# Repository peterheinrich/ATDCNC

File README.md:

# ATDCNC
A Tiny Desktop CNC Built from Readily Available Parts

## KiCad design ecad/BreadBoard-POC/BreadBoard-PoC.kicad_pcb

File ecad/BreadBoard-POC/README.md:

# GRBL Compatible Controller

This tiny desktop CNC will use GRBL to interpret G-Code.

## PoC Breadboard Setup
* Uses now obsolete L6208N (PDIP) stepper driver. L6208D is still available for SMD design iteration. Basically any step/dir driver will do!
* 1.5A max phase current with a 20V supply for sufficient headroom.
* ATMega328 microcontroller for step generation.
* 2.54mm (100mil) design restriction for easy breadboard prototyping.

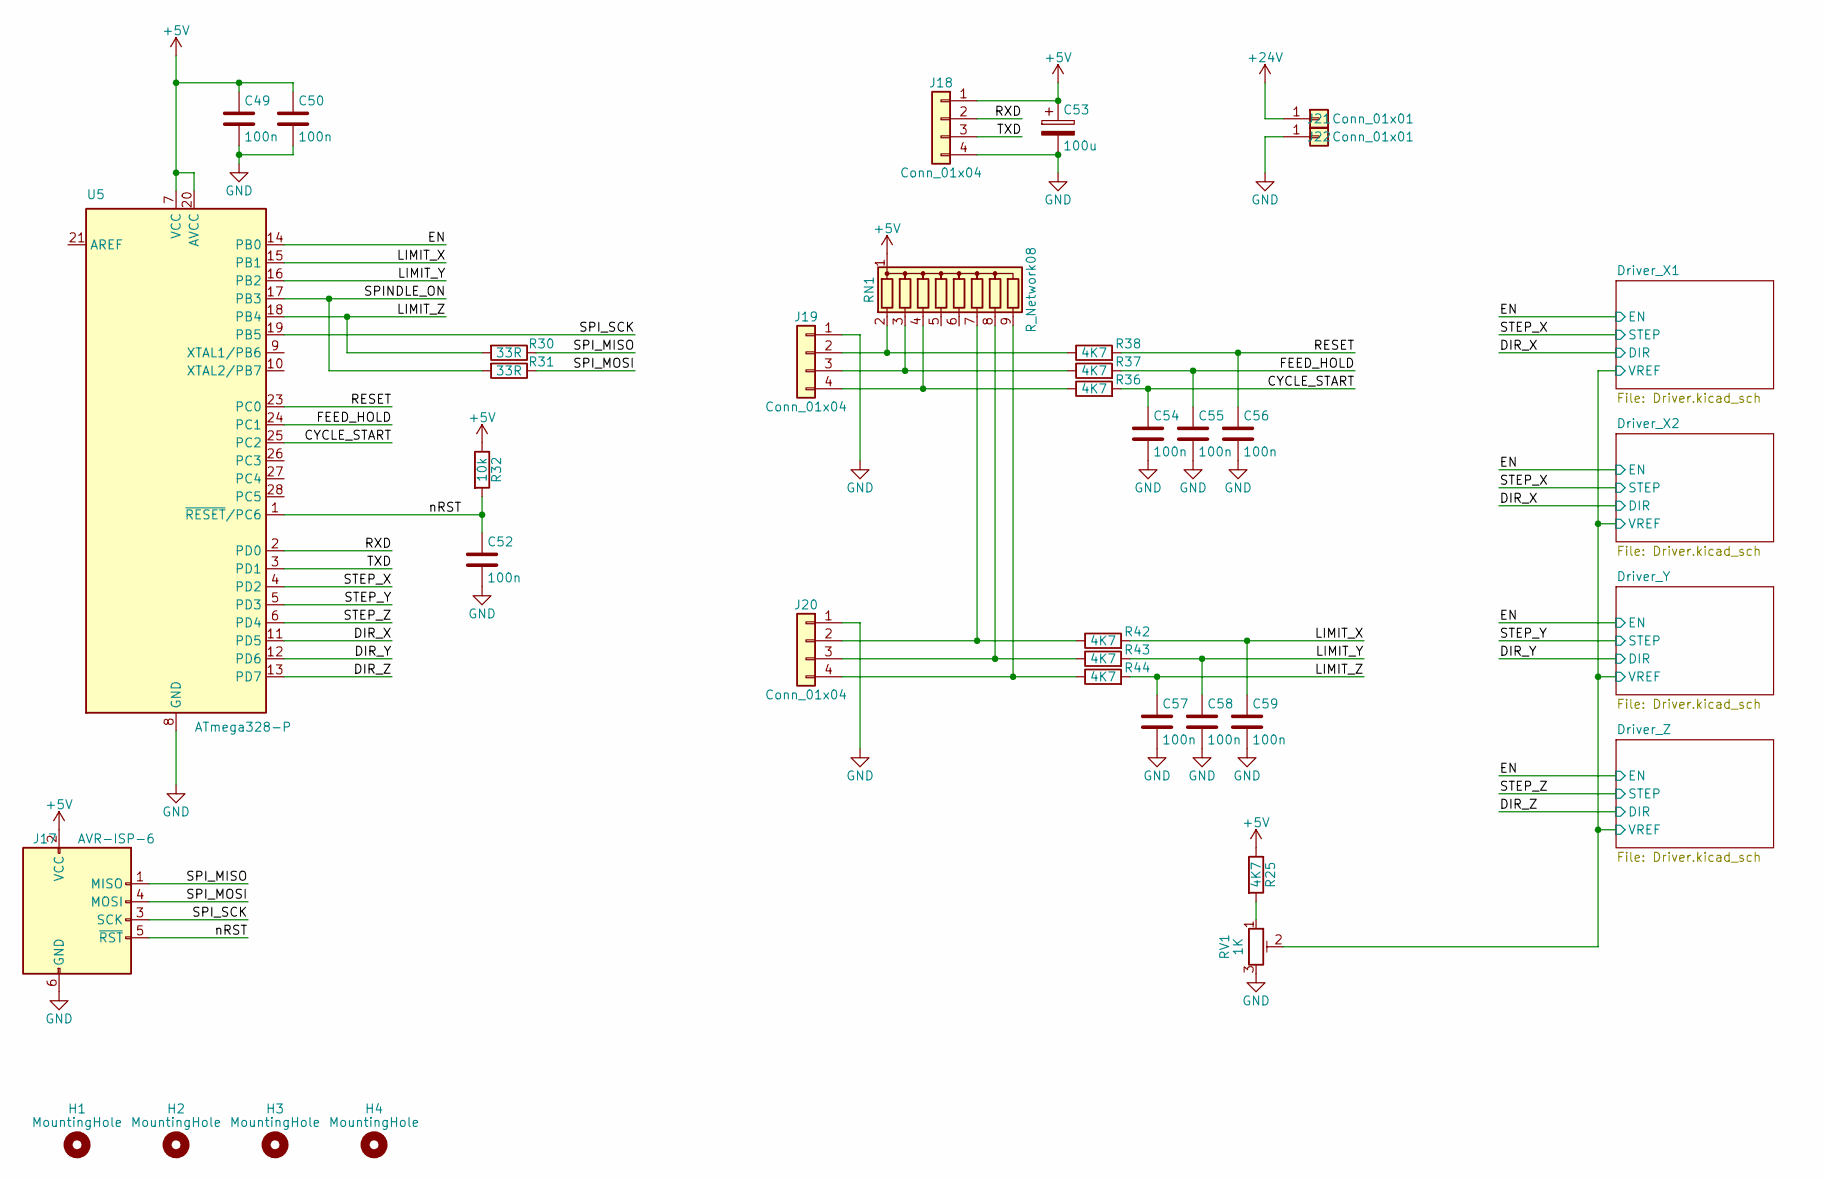
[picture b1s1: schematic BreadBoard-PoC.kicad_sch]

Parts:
C49, C50, C52, C54, C55, C56, C57, C58, C59: 100n; C_Rect_L4.6mm_W2.0mm_P2.50mm_MKS02_FKP02
C53: 100u; CP_Radial_D6.3mm_P2.50mm
H1, H2, H3, H4: MountingHole; MountingHole_3.2mm_M3_DIN965
J17: AVR-ISP-6; PinHeader_2x03_P2.54mm_Vertical
J18, J19, J20: Conn_01x04; PinHeader_1x04_P2.54mm_Vertical
J21, J22: Conn_01x01; PinHeader_1x01_P2.54mm_Vertical
R25, R36, R37, R38, R42, R43, R44: 4K7; R_Axial_DIN0207_L6.3mm_D2.5mm_P2.54mm_Vertical
R30, R31: 33R; R_Axial_DIN0207_L6.3mm_D2.5mm_P2.54mm_Vertical
R32: 10k; R_Axial_DIN0207_L6.3mm_D2.5mm_P2.54mm_Vertical
RN1: R_Network08; R_Array_SIP9
RV1: 1K; Potentiometer_Bourns_3266W_Vertical
U5: ATmega328-P; DIP-28_W7.62mm_LongPads

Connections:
+5V: C49.1, C50.1, C53.1, J17.2 (VCC), J18.1, R25.1, R32.1, RN1.1 (common), U5.7 (VCC), U5.20 (AVCC); also elsewhere on the board
+24V: J21.1; also elsewhere on the board
/CYCLE_START: C54.1, R36.2, U5.25 (PC2)
/DIR_X: U5.11 (PD5); also elsewhere on the board
/DIR_Y: U5.12 (PD6); also elsewhere on the board
/DIR_Z: U5.13 (PD7); also elsewhere on the board
/Driver_X1/VREF: RV1.2; also elsewhere on the board
/EN: U5.14 (PB0); also elsewhere on the board
/FEED_HOLD: C55.1, R37.2, U5.24 (PC1)
/LIMIT_X: C59.1, R42.2, U5.15 (PB1)
/LIMIT_Y: C58.1, R43.2, U5.16 (PB2)
/LIMIT_Z: C57.1, R30.2, R44.2, U5.18 (PB4)
/RESET: C56.1, R38.2, U5.23 (PC0)
/RXD: J18.2, U5.2 (PD0)
/SPINDLE_ON: R31.2, U5.17 (PB3)
/SPI_MISO: J17.1 (MISO), R30.1
/SPI_MOSI: J17.4 (MOSI), R31.1
/SPI_SCK: J17.3 (SCK), U5.19 (PB5)
/STEP_X: U5.4 (PD2); also elsewhere on the board
/STEP_Y: U5.5 (PD3); also elsewhere on the board
/STEP_Z: U5.6 (PD4); also elsewhere on the board
/TXD: J18.3, U5.3 (PD1)
/nRST: C52.1, J17.5 (~RST), R32.2, U5.1 (~RESET/PC6)
GND: C49.2, C50.2, C52.2, C53.2, C54.2, C55.2, C56.2, C57.2, C58.2, C59.2, J17.6 (GND), J18.4, J19.1, J20.1, J22.1, RV1.3, U5.8 (GND), U5.22 (GND); also elsewhere on the board
unnamed: J19.2, R38.1, RN1.2 (R1)
unnamed: J19.3, R37.1, RN1.3 (R2)
unnamed: J19.4, R36.1, RN1.4 (R3)
unnamed: J20.2, R42.1, RN1.7 (R6)
unnamed: J20.3, R43.1, RN1.8 (R7)
unnamed: J20.4, R44.1, RN1.9 (R8)
unnamed: R25.2, RV1.1

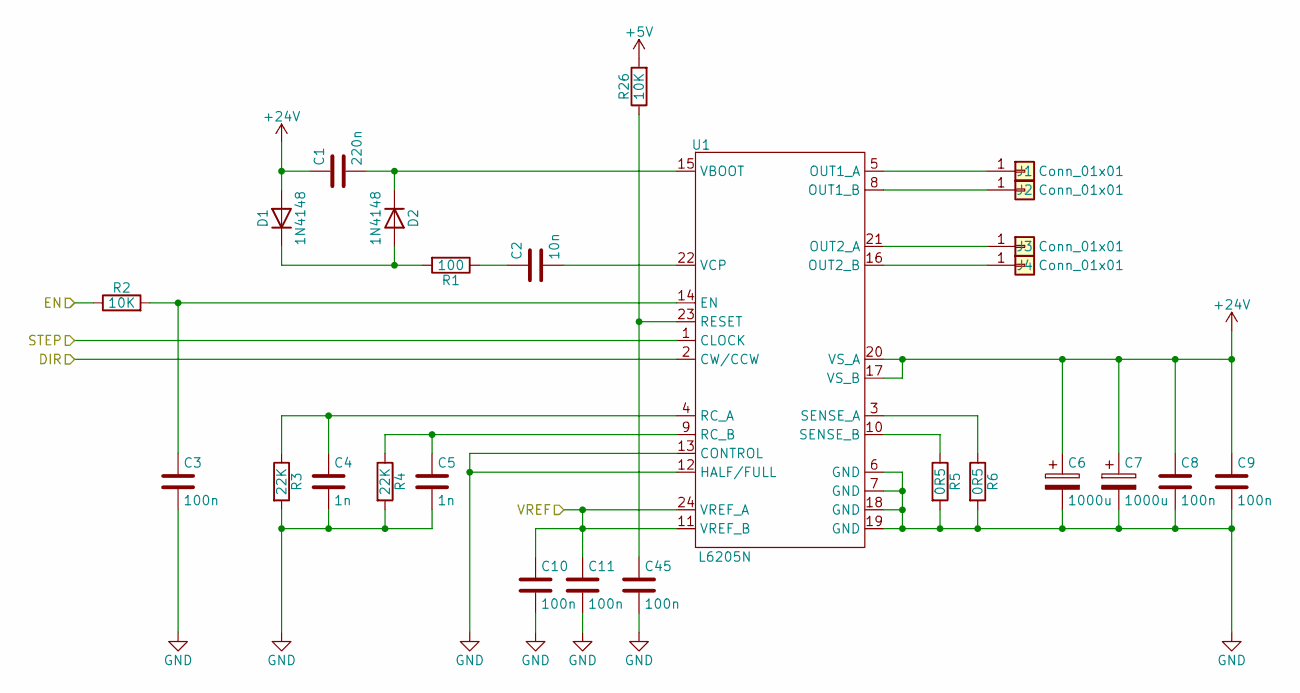
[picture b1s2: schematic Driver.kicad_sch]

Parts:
C1: 220n; C_Rect_L7.0mm_W2.5mm_P5.00mm
C2: 10n; C_Rect_L4.6mm_W2.0mm_P2.50mm_MKS02_FKP02
C3, C8, C9, C10, C11, C45: 100n; C_Rect_L4.6mm_W2.0mm_P2.50mm_MKS02_FKP02
C4, C5: 1n; C_Rect_L4.6mm_W2.0mm_P2.50mm_MKS02_FKP02
C6, C7: 1000u; CP_Radial_D10.0mm_P5.00mm
D1, D2: 1N4148; D_A-405_P2.54mm_Vertical_AnodeUp
J1, J2, J3, J4: Conn_01x01; PinHeader_1x01_P2.54mm_Vertical
R1: 100; R_Axial_DIN0207_L6.3mm_D2.5mm_P2.54mm_Vertical
R2, R26: 10K; R_Axial_DIN0207_L6.3mm_D2.5mm_P2.54mm_Vertical
R3, R4: 22K; R_Axial_DIN0207_L6.3mm_D2.5mm_P2.54mm_Vertical
R5, R6: 0R5; R_Axial_DIN0207_L6.3mm_D2.5mm_P10.16mm_Horizontal
U1: L6205N; DIP-24_W7.62mm_LongPads

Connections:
+5V: R26.2; also elsewhere on the board
+24V: C1.1, C6.1, C7.1, C8.1, C9.1, D1.2 (A), U1.17 (VS_B), U1.20 (VS_A); also elsewhere on the board
/DIR_X: U1.2 (CW/CCW); also elsewhere on the board
/Driver_X1/VREF: C10.1, C11.1, U1.11 (VREF_B), U1.24 (VREF_A); also elsewhere on the board
/EN: R2.1; also elsewhere on the board
/STEP_X: U1.1 (CLOCK); also elsewhere on the board
GND: C3.2, C4.2, C5.2, C6.2, C7.2, C8.2, C9.2, C10.2, C11.2, C45.2, R3.2, R4.2, R5.2, R6.2, U1.6 (GND), U1.7 (GND), U1.12 (HALF/FULL), U1.13 (CONTROL), U1.18 (GND), U1.19 (GND); also elsewhere on the board
unnamed: C2.1, R1.1
unnamed: D1.1 (K), D2.2 (A), R1.2
unnamed: C1.2, D2.1 (K), U1.15 (VBOOT)
unnamed: J1.1, U1.5 (OUT1_A)
unnamed: J2.1, U1.8 (OUT1_B)
unnamed: J3.1, U1.21 (OUT2_A)
unnamed: J4.1, U1.16 (OUT2_B)
unnamed: C3.1, R2.2, U1.14 (EN)
unnamed: C4.1, R3.1, U1.4 (RC_A)
unnamed: C5.1, R4.1, U1.9 (RC_B)
unnamed: C45.1, R26.1, U1.23 (RESET)
unnamed: R6.1, U1.3 (SENSE_A)
unnamed: R5.1, U1.10 (SENSE_B)
unnamed: C2.2, U1.22 (VCP)

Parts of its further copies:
C12, C23, C34: 220n; C_Rect_L7.0mm_W2.5mm_P5.00mm
C13, C24, C35: 10n; C_Rect_L4.6mm_W2.0mm_P2.50mm_MKS02_FKP02
C14, C19, C20, C21, C22, C25, C30, C31, C32, C33, C36, C41, C42, C43, C44, C46, C47, C48: 100n; C_Rect_L4.6mm_W2.0mm_P2.50mm_MKS02_FKP02
C15, C16, C26, C27, C37, C38: 1n; C_Rect_L4.6mm_W2.0mm_P2.50mm_MKS02_FKP02
C17, C18, C28, C29, C39, C40: 1000u; CP_Radial_D10.0mm_P5.00mm
D3, D4, D5, D6, D7, D8: 1N4148; D_A-405_P2.54mm_Vertical_AnodeUp
J5, J6, J7, J8, J9, J10, J11, J12, J13, J14, J15, J16: Conn_01x01; PinHeader_1x01_P2.54mm_Vertical
R7, R13, R19: 100; R_Axial_DIN0207_L6.3mm_D2.5mm_P2.54mm_Vertical
R8, R14, R20, R27, R28, R29: 10K; R_Axial_DIN0207_L6.3mm_D2.5mm_P2.54mm_Vertical
R9, R10, R15, R16, R21, R22: 22K; R_Axial_DIN0207_L6.3mm_D2.5mm_P2.54mm_Vertical
R11, R12, R17, R18, R23, R24: 0R5; R_Axial_DIN0207_L6.3mm_D2.5mm_P10.16mm_Horizontal
U2, U3, U4: L6205N; DIP-24_W7.62mm_LongPads

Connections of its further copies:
+5V: R27.2, R28.2, R29.2; also elsewhere on the board
+24V: C12.1, C17.1, C18.1, C19.1, C20.1, C23.1, C28.1, C29.1, C30.1, C31.1, C34.1, C39.1, C40.1, C41.1, C42.1, D3.2 (A), D5.2 (A), D7.2 (A), U2.17 (VS_B), U2.20 (VS_A), U3.17 (VS_B), U3.20 (VS_A), U4.17 (VS_B), U4.20 (VS_A); also elsewhere on the board
/DIR_X: U2.2 (CW/CCW); also elsewhere on the board
/DIR_Y: U3.2 (CW/CCW); also elsewhere on the board
/DIR_Z: U4.2 (CW/CCW); also elsewhere on the board
/Driver_X1/VREF: C21.1, C22.1, C32.1, C33.1, C43.1, C44.1, U2.11 (VREF_B), U2.24 (VREF_A), U3.11 (VREF_B), U3.24 (VREF_A), U4.11 (VREF_B), U4.24 (VREF_A); also elsewhere on the board
/EN: R8.1, R14.1, R20.1; also elsewhere on the board
/STEP_X: U2.1 (CLOCK); also elsewhere on the board
/STEP_Y: U3.1 (CLOCK); also elsewhere on the board
/STEP_Z: U4.1 (CLOCK); also elsewhere on the board
GND: C14.2, C15.2, C16.2, C17.2, C18.2, C19.2, C20.2, C21.2, C22.2, C25.2, C26.2, C27.2, C28.2, C29.2, C30.2, C31.2, C32.2, C33.2, C36.2, C37.2, C38.2, C39.2, C40.2, C41.2, C42.2, C43.2, C44.2, C46.2, C47.2, C48.2, R9.2, R10.2, R11.2, R12.2, R15.2, R16.2, R17.2, R18.2, R21.2, R22.2, R23.2, R24.2, U2.6 (GND), U2.7 (GND), U2.12 (HALF/FULL), U2.13 (CONTROL), U2.18 (GND), U2.19 (GND), U3.6 (GND), U3.7 (GND), U3.12 (HALF/FULL), U3.13 (CONTROL), U3.18 (GND), U3.19 (GND), U4.6 (GND), U4.7 (GND), U4.12 (HALF/FULL), U4.13 (CONTROL), U4.18 (GND), U4.19 (GND); also elsewhere on the board
unnamed: C13.1, R7.1
unnamed: C24.1, R13.1
unnamed: C35.1, R19.1
unnamed: D3.1 (K), D4.2 (A), R7.2
unnamed: C12.2, D4.1 (K), U2.15 (VBOOT)
unnamed: D5.1 (K), D6.2 (A), R13.2
unnamed: C23.2, D6.1 (K), U3.15 (VBOOT)
unnamed: D7.1 (K), D8.2 (A), R19.2
unnamed: C34.2, D8.1 (K), U4.15 (VBOOT)
unnamed: J5.1, U2.5 (OUT1_A)
unnamed: J6.1, U2.8 (OUT1_B)
unnamed: J7.1, U2.21 (OUT2_A)
unnamed: J8.1, U2.16 (OUT2_B)
unnamed: J9.1, U3.5 (OUT1_A)
unnamed: J10.1, U3.8 (OUT1_B)
unnamed: J11.1, U3.21 (OUT2_A)
unnamed: J12.1, U3.16 (OUT2_B)
unnamed: J13.1, U4.5 (OUT1_A)
unnamed: J14.1, U4.8 (OUT1_B)
unnamed: J15.1, U4.21 (OUT2_A)
unnamed: J16.1, U4.16 (OUT2_B)
unnamed: C14.1, R8.2, U2.14 (EN)
unnamed: C15.1, R9.1, U2.4 (RC_A)
unnamed: C16.1, R10.1, U2.9 (RC_B)
unnamed: C46.1, R27.1, U2.23 (RESET)
unnamed: R12.1, U2.3 (SENSE_A)
unnamed: R11.1, U2.10 (SENSE_B)
unnamed: C13.2, U2.22 (VCP)
unnamed: C25.1, R14.2, U3.14 (EN)
unnamed: C26.1, R15.1, U3.4 (RC_A)
unnamed: C27.1, R16.1, U3.9 (RC_B)
unnamed: C47.1, R28.1, U3.23 (RESET)
unnamed: R18.1, U3.3 (SENSE_A)
unnamed: R17.1, U3.10 (SENSE_B)
unnamed: C24.2, U3.22 (VCP)
unnamed: C36.1, R20.2, U4.14 (EN)
unnamed: C37.1, R21.1, U4.4 (RC_A)
unnamed: C38.1, R22.1, U4.9 (RC_B)
unnamed: C48.1, R29.1, U4.23 (RESET)
unnamed: R24.1, U4.3 (SENSE_A)
unnamed: R23.1, U4.10 (SENSE_B)
unnamed: C35.2, U4.22 (VCP)

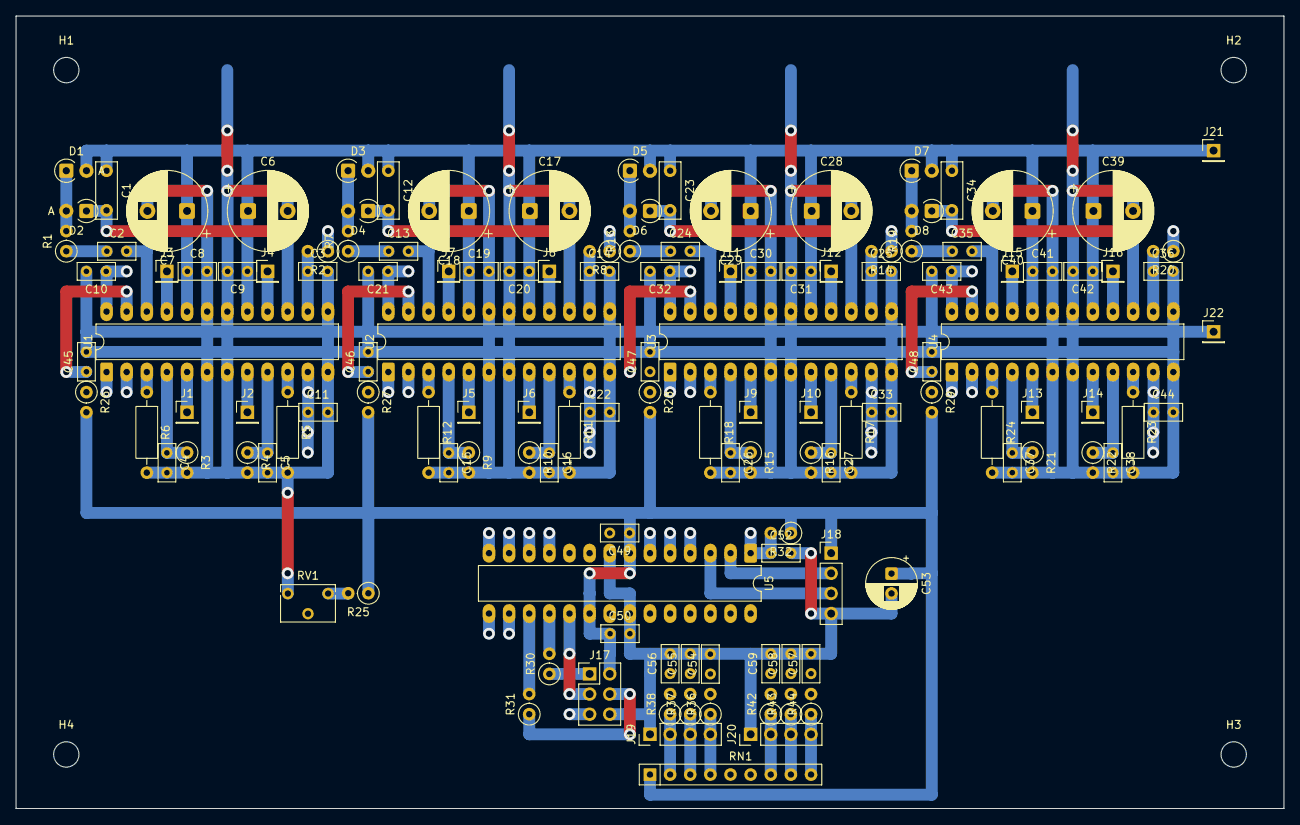
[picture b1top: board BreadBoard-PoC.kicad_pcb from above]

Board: 2 copper layers, 160.0 x 100.0 mm, 137 parts (0 on the bottom side), 87 nets.

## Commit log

2025-09-25 Designing L6208 Drivers
2025-09-26 Finalizing POC placement and routing.
